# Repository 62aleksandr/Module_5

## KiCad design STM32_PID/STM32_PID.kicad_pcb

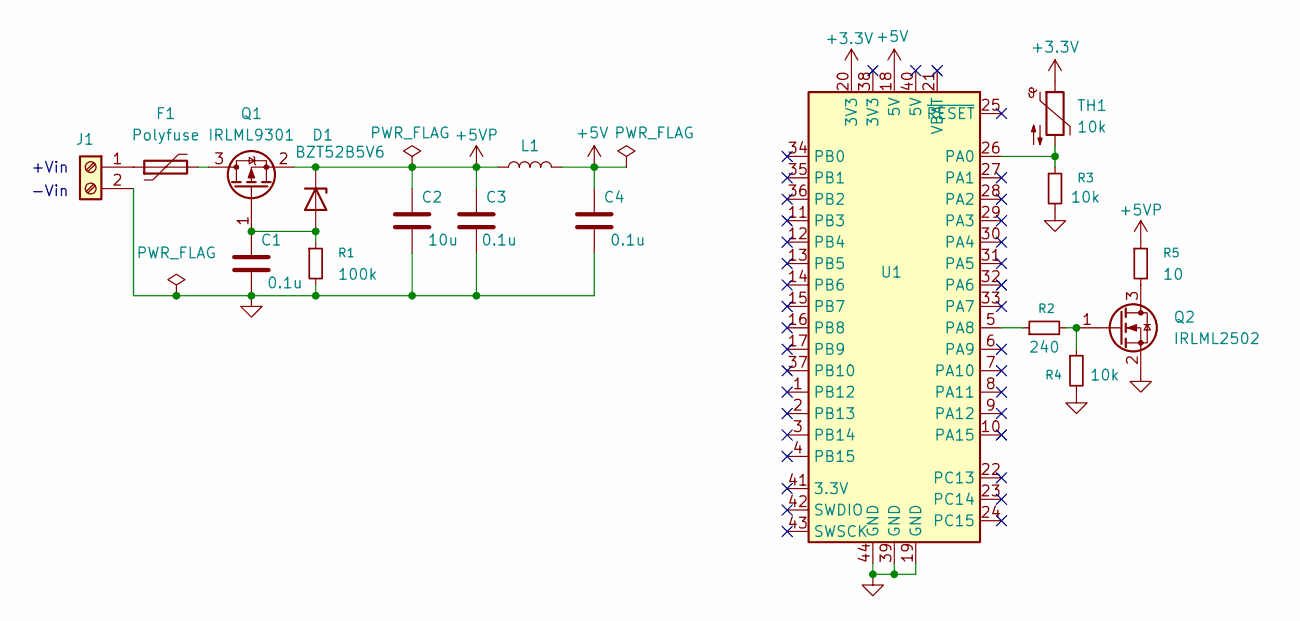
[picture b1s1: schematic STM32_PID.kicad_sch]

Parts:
C1, C3, C4: 0.1u; C_0805_2012Metric
C2: 10u; C_0805_2012Metric
D1: BZT52B5V6; D_SOD-123F
F1: Polyfuse; Fuse_Bourns_MF-SM_7.98x5.44mm
J1: Screw_Terminal_01x02; TerminalBlock_Phoenix_MKDS-1,5-2-5.08_1x02_P5.08mm_Horizont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
L1: L; L_0805_2012Metric
Q1: IRLML9301; SOT-23
Q2: IRLML2502; SOT-23
R1: 100k; R_0805_2012Metric
R2: 240; R_0805_2012Metric
R3, R4: 10k; R_0805_2012Metric
R5: 10; R_Axial_Power_L20.0mm_W6.4mm_P5.08mm_Vertical
TH1: 10k; R_Axial_DIN0204_L3.6mm_D1.6mm_P2.54mm_Vertical
U1: BlackPill_STLINK; Mini_F4X1_STM32

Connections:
+3.3V: TH1.1, U1.20 (3V3)
+5V: C4.1, L1.2, U1.18 (5V)
+5VP: C2.1, C3.1, D1.1 (K), L1.1, Q1.2 (S), R5.1
<NO NET>: C1.2, C2.2, C3.2, C4.2, J1.2, Q2.2 (S), R1.2, R3.2, R4.2, U1.19 (GND), U1.39 (GND), U1.44 (GND)
unnamed: C1.1, D1.2 (A), Q1.1 (G), R1.1
unnamed: F1.1, J1.1
unnamed: F1.2, Q1.3 (D)
unnamed: Q2.3 (D), R5.2
unnamed: Q2.1 (G), R2.2, R4.1
unnamed: R3.1, TH1.2, U1.26 (PA0)
unnamed: R2.1, U1.5 (PA8)

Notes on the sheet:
+Vin
-Vin

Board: 2 copper layers, 17 parts (0 on the bottom side), 11 nets, no tracks yet.

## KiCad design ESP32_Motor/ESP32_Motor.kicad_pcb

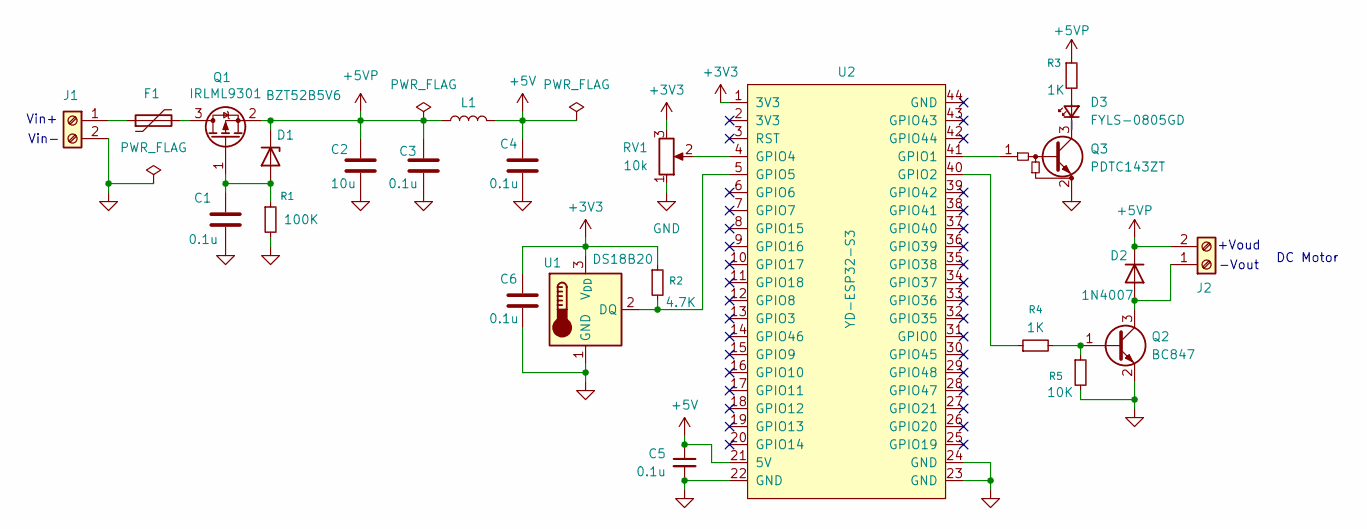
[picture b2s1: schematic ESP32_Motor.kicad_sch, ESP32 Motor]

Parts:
C1, C3, C4, C5, C6: 0.1u; C_0805_2012Metric
C2: 10u; C_0805_2012Metric
D1: BZT52B5V6; D_SOD-123F
D2: 1N4007; D_DO-41_SOD81_P10.16mm_Horizontal
D3: FYLS-0805GD; LED_0805_2012Metric
F1: Polyfuse; Fuse_Bourns_MF-SM_7.98x5.44mm
J1, J2: Screw_Terminal_01x02; TerminalBlock_Phoenix_MKDS-1,5-2-5.08_1x02_P5.08mm_Horizont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
L1: L; L_0805_2012Metric
Q1: IRLML9301; SOT-23
Q2: BC847; SOT-23
Q3: PDTC143ZT; SOT-23
R1: 100K; R_0805_2012Metric_Pad1.20x1.40mm_HandSolder
R2: 4.7K; R_0805_2012Metric_Pad1.20x1.40mm_HandSolder
R3, R4: 1K; R_0805_2012Metric_Pad1.20x1.40mm_HandSolder
R5: 10K; R_0805_2012Metric_Pad1.20x1.40mm_HandSolder
RV1: 10k; Potentiometer_ACP_CA14-VSMD_Vertical
U1: DS18B20; TO-92_Inline
U2: YD-ESP32-S3

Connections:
+3V3: C6.1, R2.1, RV1.3, U1.3 (V_{DD}), U2.1 (3V3)
+5V: C4.1, C5.1, L1.2, U2.21 (5V)
+5VP: C2.1, C3.1, D1.1 (K), D2.1 (K), J2.2, L1.1, Q1.2 (S), R3.1
GND: C1.2, C2.2, C3.2, C4.2, C5.2, C6.2, J1.2, Q2.2 (E), Q3.2 (E), R1.2, R5.2, RV1.1, U1.1 (GND), U2.22 (GND), U2.23 (GND), U2.24 (GND)
unnamed: C1.1, D1.2 (A), Q1.1 (G), R1.1
unnamed: D2.2 (A), J2.1, Q2.3 (C)
unnamed: D3.2 (A), R3.2
unnamed: D3.1 (K), Q3.3 (C)
unnamed: F1.1, J1.1
unnamed: F1.2, Q1.3 (D)
unnamed: Q2.1 (B), R4.2, R5.1
unnamed: Q3.1 (B), U2.41 (GPIO1)
unnamed: R2.2, U1.2 (DQ), U2.5 (GPIO5)
unnamed: R4.1, U2.40 (GPIO2)
unnamed: RV1.2, U2.4 (GPIO4)

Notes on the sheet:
Vin-
-Vout
DC Motor
Vin+
+Voud

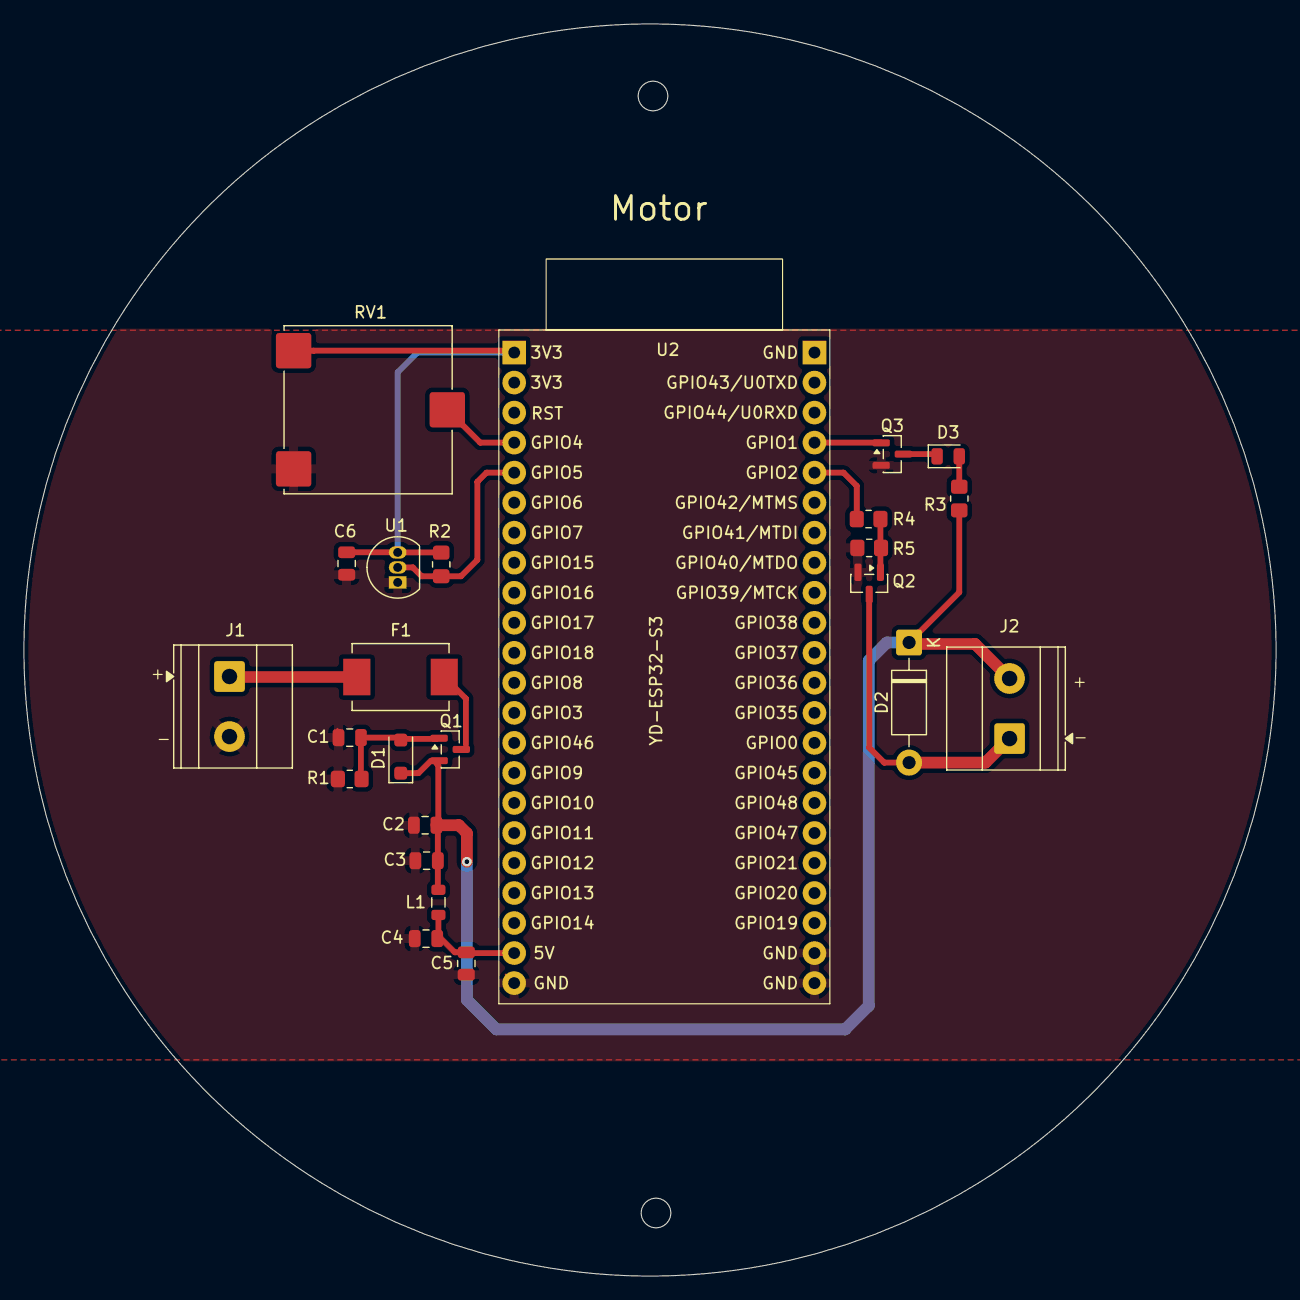
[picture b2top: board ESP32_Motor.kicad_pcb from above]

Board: 2 copper layers, 105.9 x 105.9 mm, 24 parts (0 on the bottom side), 15 nets.
